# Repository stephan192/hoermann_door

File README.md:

# hoermann_door
Control Hörmann doors drives directly via MQTT from Home Assistant

Inspired by https://blog.bouni.de/posts/2018/hoerrmann-uap1/

**USE AT YOUR OWN RISK!**

# Overview

This repo contains the pcb files as well as the software to build an interface device which connects Hörmann door drives like the Supramatic E3 to Home Assistant. The interface device emulates an UAP1 to interact with the door drive. Additionally a BME280 can be connected via I2C to measure temperature, humidity and pressure.

The door drive is automatically added to Home Assistant via [MQTT Discovery](https://www.home-assistant.io/docs/mqtt/discovery/).

# Folder structure

* `board`: The Eagle schematic and board files
* `docs`: Documentation
* `esp8266`: Arduino project. Communication to Home Assistant via wifi and mqtt
* `pic16`: MPLabX project. Communication with door drive via Hörmann bus

# Thing to do first

1. Get a pcb
    * Optionally, get BME280 sensor pcb
    * Supply pcb with 24V via pins 2 & 3 of `J1`
    * Check if 5V and 3.3V are fine
1. Get tools listed below
1. Rename esp8266/config_template.h to esp8266/config.h and adjust to your environment
1. Add `esp8266` boards to Arduino IDE
    * Open Preferences window
    * Enter http://arduino.esp8266.com/stable/package_esp8266com_index.json into Additional Board Manager URLs field. You can add multiple URLs, separating them with commas.
    * Open Boards Manager from Tools > Board menu and find `esp8266` platform.
    * Click install button.
    * Select `NodeMCU 1.0 (ESP-12E Module)` as board
1. Add Libraries to Arduino IDE
    * Open Sketch > Include library -> Manage libraries...
    * Install `PubSubClient` (tested with version 2.8.0)
    * Install `PubSubClientTools` (tested with version 0.6.0)
    * Install `Adafruit Unified Sensor` (tested with version 1.1.4)
    * Install `Adafruit BME280 Library` (tested with version 2.1.2)
1. First flashing of `esp8266`
    * Get a cheap USB-UART converter (like the ones with a `CP210x`)
    * Connect the converter to `SV3` (RX, TX and GND)
    * Short `JP1` (Boot mode)
    * Power up board. If board was powered before reset `esp8266` by shorting `JP2`(Reset) for a short time
1. Flashing `pic16`
    * Get a Microchip programmer which supports the pic16 (PICkit3, ICD3, ...)
    * Connect the programmer to `SV1`
    * Open MPLabX and click on File -> Open Project
    * Select `pic16` subfolder (chip icon)
    * Click Clean an Build Main Project
    * Click Make and Program Device Main Project

# Used tools

## Schematic and board
* Eagle 7.2.0

## ESP8266
* Arduino IDE 1.8.13
* USB-UART converter

## PIC16
* MPLabX v5.45
* Device Family Pack PIC16F1xxxx_DFP 1.5.133
* XC8 v2.32
* PICkit3

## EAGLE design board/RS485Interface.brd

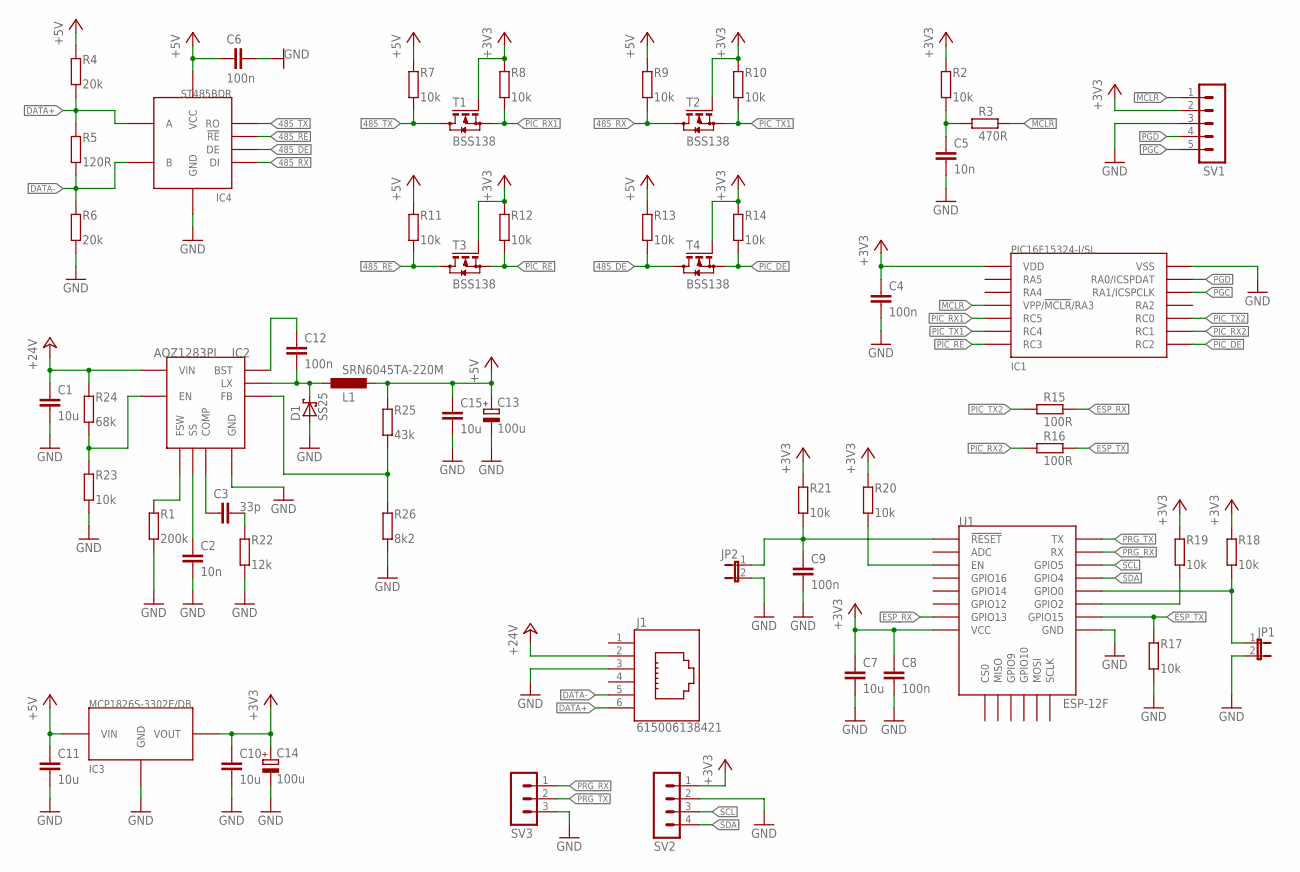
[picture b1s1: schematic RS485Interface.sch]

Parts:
C1, C7, C10, C11, C15: 10u; C0805
C2, C5: 10n; C0805
C3: 33p; C0805
C4, C6, C8, C9, C12: 100n; C0805
C13, C14: 100u; UCL6.3
D1: SS25; DO-214AA
IC1: PIC16F15324-I/SL; SOIC14
IC2: AOZ1283PI; SO8+PAD
IC3: MCP1826S-3302E/DB; SOT-223-3
IC4: ST485BDR; SOIC8
J1: 615006138421
JP1, JP2: JP1E; JP1
L1: SRN6045TA-220M; SRN6045TA
R1: 200k; R0805
R2, R7, R8, R9, R10, R11, R12, R13, R14, R17, R18, R19, R20, R21, R23: 10k; R0805
R3: 470R; R0805
R4, R6: 20k; R0805
R5: 120R; R0805
R15, R16: 100R; R0805
R22: 12k; R0805
R24: 68k; R0805
R25: 43k; R0805
R26: 8k2; R0805
SV1: MA05-1
SV2: MA04-1
SV3: MA03-1
T1, T2, T3, T4: BSS138; SOT-23
U1: ESP-12F; ESP12E-SMD

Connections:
485_DE: IC4.P3 (DE), R13.1, T4.P3 (D)
485_RX: IC4.P4 (DI), R9.1, T2.P3 (D)
485_TX: IC4.P1 (RO), R7.1, T1.P3 (D)
!485_RE: IC4.P2 (!RE), R11.1, T3.P3 (D)
!MCLR: IC1.P4 (VPP/!MCLR!/RA3), R3.1, SV1.1
!PIC_RE: IC1.P7 (RC3), R12.1, T3.P2 (S)
!RESET: C9.1, JP2.1, R21.1, U1.RESET (!RESET)
+3V3: C4.1, C7.1, C8.1, C10.1, C14.+, IC1.P1 (VDD), IC3.P3 (VOUT), R2.2, R8.2, R10.2, R12.2, R14.2, R18.2, R19.2, R20.2, R21.2, SV1.2, SV2.1, T1.P1 (G), T2.P1 (G), T3.P1 (G), T4.P1 (G), U1.VCC
+5V: C6.1, C11.1, C13.+, C15.1, IC3.P1 (VIN), IC4.P8 (VCC), L1.P$1 (1), R4.2, R7.2, R9.2, R11.2, R13.2, R25.2
+24V: C1.1, IC2.PAD (VIN), J1.2 (5), R24.2
DATA+: IC4.P6 (A), J1.6 (1), R4.1, R5.2
DATA-: IC4.P7 (B), J1.5 (2), R5.1, R6.2
EN: R20.1, U1.EN
ESP_RX: R15.1, U1.GPIO13
ESP_TX: R16.1, R17.2, U1.GPIO15
GND: C1.2, C2.2, C4.2, C5.2, C6.2, C7.2, C8.2, C9.2, C10.2, C11.2, C13.-, C14.-, C15.2, D1.A, IC1.P14 (VSS), IC2.P3 (GND), IC3.P2 (GND), IC3.P4 (GND), IC4.P5 (GND), J1.3 (4), JP1.2, JP2.2, R1.1, R6.1, R17.1, R22.1, R23.1, R26.1, SV1.3, SV2.2, SV3.3, U1.GND
GPIO0: JP1.1, R18.1, U1.GPIO0
GPIO2: R19.1, U1.GPIO2
LX: C12.2, D1.C, IC2.P1 (LX), L1.P$2 (2)
unnamed: IC2.P8 (EN), R23.2, R24.1
unnamed: C3.1, IC2.P5 (COMP)
unnamed: C5.1, R2.1, R3.2
unnamed: C3.2, R22.2
unnamed: C2.1, IC2.P7 (SS)
unnamed: IC2.P4 (FSW), R1.2
unnamed: IC2.P6 (FB), R25.1, R26.2
unnamed: C12.1, IC2.P2 (BST)
PGC: IC1.P12 (RA1/ICSPCLK), SV1.5
PGD: IC1.P13 (RA0/ICSPDAT), SV1.4
PIC_DE: IC1.P8 (RC2), R14.1, T4.P2 (S)
PIC_RX1: IC1.P5 (RC5), R8.1, T1.P2 (S)
PIC_RX2: IC1.P9 (RC1), R16.2
PIC_TX1: IC1.P6 (RC4), R10.1, T2.P2 (S)
PIC_TX2: IC1.P10 (RC0), R15.2
PRG_RX: SV3.1, U1.RXD0 (RX)
PRG_TX: SV3.2, U1.TXD0 (TX)
SCL: SV2.3, U1.GPIO5
SDA: SV2.4, U1.GPIO4

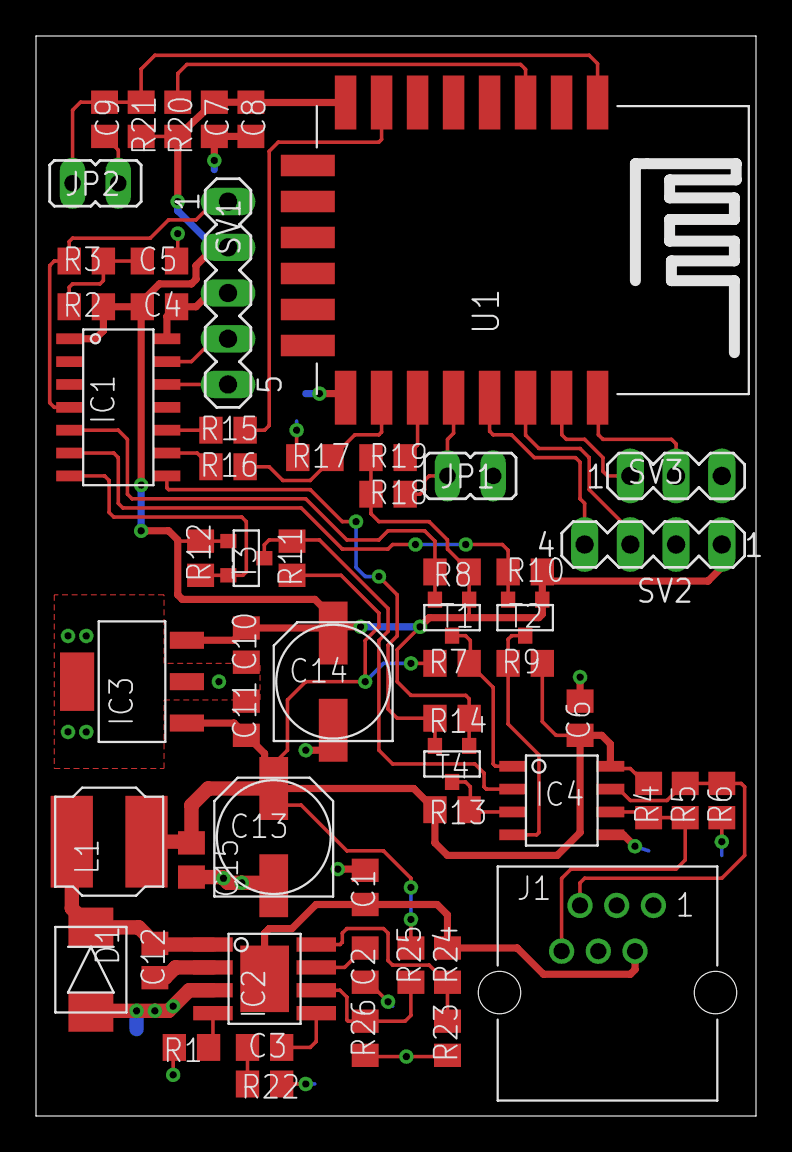
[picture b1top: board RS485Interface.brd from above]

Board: 2 copper layers, 40.0 x 60.0 mm, 58 parts (0 on the bottom side), 38 nets.

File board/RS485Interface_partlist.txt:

Partlist

Exported from RS485Interface.sch at 06.07.2022 19:41:02

EAGLE Version 7.2.0 Copyright (c) 1988-2014 CadSoft

Assembly variant: 

Part     Value             Device            Package      Library                Sheet

C1       10u               C-EUC0805         C0805        rcl                    1
C2       10n               C-EUC0805         C0805        rcl                    1
C3       33p               C-EUC0805         C0805        rcl                    1
C4       100n              C-EUC0805         C0805        rcl                    1
C5       10n               C-EUC0805         C0805        rcl                    1
C6       100n              C-EUC0805         C0805        rcl                    1
C7       10u               C-EUC0805         C0805        rcl                    1
C8       100n              C-EUC0805         C0805        rcl                    1
C9       100n              C-EUC0805         C0805        rcl                    1
C10      10u               C-EUC0805         C0805        rcl                    1
C11      10u               C-EUC0805         C0805        rcl                    1
C12      100n              C-EUC0805         C0805        rcl                    1
C13      100u              UCL               UCL6.3       RS485Interface         1
C14      100u              UCL               UCL6.3       RS485Interface         1
C15      10u               C-EUC0805         C0805        rcl                    1
D1       SS25              SS25              DO-214AA     RS485Interface         1
IC1      PIC16F15324-I/SL  PIC16F15324-I/SL  SOIC14       RS485Interface         1
IC2      AOZ1283PI         AOZ1283PI         SO8+PAD      RS485Interface         1
IC3      MCP1826S-3302E/DB MCP1826S-3302E/DB SOT-223-3    RS485Interface         1
IC4      ST485BDR          ST485BDR          SOIC8        RS485Interface         1
J1       615006138421      615006138421      615006138421 InputOutputIO (rev19b) 1
JP1                        JP1E              JP1          jumper                 1
JP2                        JP1E              JP1          jumper                 1
L1       SRN6045TA-220M    SRN6045TA-220M    SRN6045TA    RS485Interface         1
R1       200k              R-EU_R0805        R0805        rcl                    1
R2       10k               R-EU_R0805        R0805        rcl                    1
R3       470R              R-EU_R0805        R0805        rcl                    1
R4       20k               R-EU_R0805        R0805        rcl                    1
R5       120R              R-EU_R0805        R0805        rcl                    1
R6       20k               R-EU_R0805        R0805        rcl                    1
R7       10k               R-EU_R0805        R0805        rcl                    1
R8       10k               R-EU_R0805        R0805        rcl                    1
R9       10k               R-EU_R0805        R0805        rcl                    1
R10      10k               R-EU_R0805        R0805        rcl                    1
R11      10k               R-EU_R0805        R0805        rcl                    1
R12      10k               R-EU_R0805        R0805        rcl                    1
R13      10k               R-EU_R0805        R0805        rcl                    1
R14      10k               R-EU_R0805        R0805        rcl                    1
R15      100R              R-EU_R0805        R0805        rcl                    1
R16      100R              R-EU_R0805        R0805        rcl                    1
R17      10k               R-EU_R0805        R0805        rcl                    1
R18      10k               R-EU_R0805        R0805        rcl                    1
R19      10k               R-EU_R0805        R0805        rcl                    1
R20      10k               R-EU_R0805        R0805        rcl                    1
R21      10k               R-EU_R0805        R0805        rcl                    1
R22      12k               R-EU_R0805        R0805        rcl                    1
R23      10k               R-EU_R0805        R0805        rcl                    1
R24      68k               R-EU_R0805        R0805        rcl                    1
R25      43k               R-EU_R0805        R0805        rcl                    1
R26      8k2               R-EU_R0805        R0805        rcl                    1
SV1                        MA05-1            MA05-1       con-lstb               1
SV2                        MA04-1            MA04-1       con-lstb               1
SV3                        MA03-1            MA03-1       con-lstb               1
T1       BSS138            BSS138            SOT-23       RS485Interface         1
T2       BSS138            BSS138            SOT-23       RS485Interface         1
T3       BSS138            BSS138            SOT-23       RS485Interface         1
T4       BSS138            BSS138            SOT-23       RS485Interface         1
U1       ESP-12F           ESP12ESMD         ESP12E-SMD   esp8266modules         1

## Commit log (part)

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2021-02-14 Sources added
2021-02-15 Closes #1
2021-02-15 Fix typos and formatting
2021-02-15 Add device_class to configuration.yaml
2021-03-17 Add gerber files
2021-04-05 Update configuration.yaml to be compatible with upcoming HA versions
2021-04-06 Update setup instructions
2021-04-25 Update link to Bouni
2021-06-18 Add toggle light #4
2022-07-06 Add partlist #9
2022-08-28 Fix array sizes
2022-08-28 Update configuration.yaml to new MQTT format
2022-09-02 docs: clarify some of the bits
    This is the result of my experiments with different settings of
    LineaMatic.
2022-09-10 Fix configuration.yaml
2022-09-18 Unify hostname definition
2022-09-21 Add MQTT Discovery
2022-09-21 Fix BME availability
2023-01-21 Add pick & place file
2023-04-22 Update docu
2023-04-22 Add stale workflow
2023-04-23 Enable dependabot
2023-12-11 Bump actions/stale from 8 to 9
    Bumps [actions/stale](https://github.com/actions/stale) from 8 to 9.
    - [Release notes](https://github.com/actions/stale/releases)
    - [Changelog](https://github.com/actions/stale/blob/main/CHANGELOG.md)
    - [Commits](https://github.com/actions/stale/compare/v8...v9)
    ---
    updated-dependencies:
2025-01-03 Use impulse command to stop motor instead of emergency stop command
2025-09-08 Bump actions/stale from 9 to 10
    Bumps [actions/stale](https://github.com/actions/stale) from 9 to 10.
    - [Release notes](https://github.com/actions/stale/releases)
    - [Changelog](https://github.com/actions/stale/blob/main/CHANGELOG.md)
    - [Commits](https://github.com/actions/stale/compare/v9...v10)
    ---
    updated-dependencies:
2025-09-09 Bump actions/stale from 9 to 10 (#28)
    Bumps [actions/stale](https://github.com/actions/stale) from 9 to 10.
    - [Release notes](https://github.com/actions/stale/releases)
    - [Changelog](https://github.com/actions/stale/blob/main/CHANGELOG.md)
    - [Commits](https://github.com/actions/stale/compare/v9...v10)
    ---
    updated-dependencies:
2026-02-02 Use default_entity_id instead of object_id
2026-04-18 Add delay between MQTT connect and subscribe
2026-04-18 Init BME before MQTT

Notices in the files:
parts and their libraries:
InputOutputIO: Copyright: Würth Elektronik
